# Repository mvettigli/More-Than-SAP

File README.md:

# More-Than-SAP

The projects starts from Ben Eater's SAP-1 build and improves memory availability and CPU functions.

Specifically it implements:
- 16-bit address bus addressable to data bus
- 16-bit stack pointer
- 16 bit program counter
- RAM 64 kByte using CY7C199
- ROM 32 kByte using AT28C256
- 8 bit instruction register
- 2 8-bit generic purpose registers
- 2 8-bit up/down counter registers with clear
- 2 8-bit shift registers with clear
- ALU with arithmetic (ADD, SUB) and logic functions (AND, OR, XOR)
- Register file of 4 units that can be addressed to ALU from 6 available
- 4-bit flag register: zero, sign, carry and overflow

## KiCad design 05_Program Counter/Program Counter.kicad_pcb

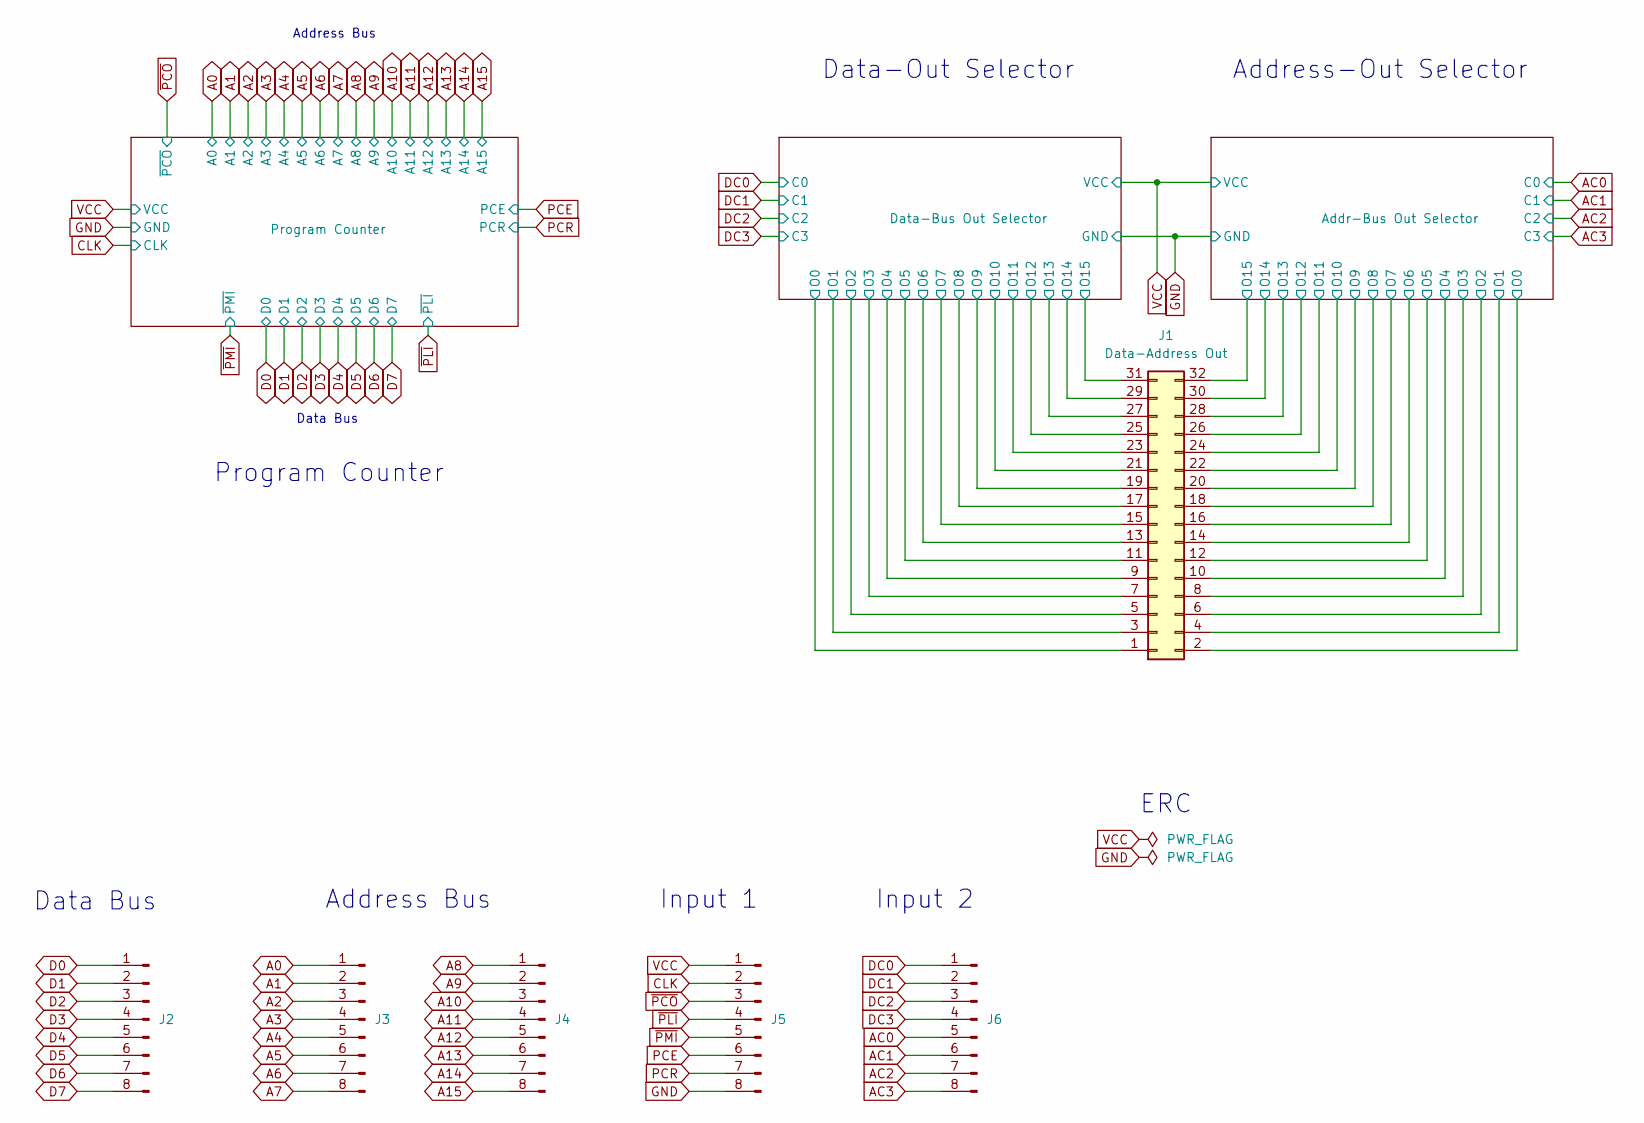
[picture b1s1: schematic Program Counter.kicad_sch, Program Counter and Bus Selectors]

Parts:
J1: Data-Address Out; PinHeader_2x16_P2.54mm_Horizontal
J2: Data bus; PinHeader_1x08_P2.54mm_Horizontal
J3: Address Bus 1; PinHeader_1x08_P2.54mm_Horizontal
J4: Address Bus 2; PinHeader_1x08_P2.54mm_Horizontal
J5: Input 1; PinHeader_1x08_P2.54mm_Horizontal
J6: Input 2; PinHeader_1x08_P2.54mm_Horizontal

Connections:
/Addr-Bus Out Selector/O0: J1.2; also elsewhere on the board
/Addr-Bus Out Selector/O1: J1.4; also elsewhere on the board
/Addr-Bus Out Selector/O2: J1.6; also elsewhere on the board
/Addr-Bus Out Selector/O3: J1.8; also elsewhere on the board
/Addr-Bus Out Selector/O4: J1.10; also elsewhere on the board
/Addr-Bus Out Selector/O5: J1.12; also elsewhere on the board
/Addr-Bus Out Selector/O6: J1.14; also elsewhere on the board
/Addr-Bus Out Selector/O7: J1.16; also elsewhere on the board
/Addr-Bus Out Selector/O8: J1.18; also elsewhere on the board
/Addr-Bus Out Selector/O9: J1.20; also elsewhere on the board
/Addr-Bus Out Selector/O10: J1.22; also elsewhere on the board
/Addr-Bus Out Selector/O11: J1.24; also elsewhere on the board
/Addr-Bus Out Selector/O12: J1.26; also elsewhere on the board
/Addr-Bus Out Selector/O13: J1.28; also elsewhere on the board
/Addr-Bus Out Selector/O14: J1.30; also elsewhere on the board
/Addr-Bus Out Selector/O15: J1.32; also elsewhere on the board
/Data-Bus Out Selector/O0: J1.1; also elsewhere on the board
/Data-Bus Out Selector/O1: J1.3; also elsewhere on the board
/Data-Bus Out Selector/O2: J1.5; also elsewhere on the board
/Data-Bus Out Selector/O3: J1.7; also elsewhere on the board
/Data-Bus Out Selector/O4: J1.9; also elsewhere on the board
/Data-Bus Out Selector/O5: J1.11; also elsewhere on the board
/Data-Bus Out Selector/O6: J1.13; also elsewhere on the board
/Data-Bus Out Selector/O7: J1.15; also elsewhere on the board
/Data-Bus Out Selector/O8: J1.17; also elsewhere on the board
/Data-Bus Out Selector/O9: J1.19; also elsewhere on the board
/Data-Bus Out Selector/O10: J1.21; also elsewhere on the board
/Data-Bus Out Selector/O11: J1.23; also elsewhere on the board
/Data-Bus Out Selector/O12: J1.25; also elsewhere on the board
/Data-Bus Out Selector/O13: J1.27; also elsewhere on the board
/Data-Bus Out Selector/O14: J1.29; also elsewhere on the board
/Data-Bus Out Selector/O15: J1.31; also elsewhere on the board
A0: J3.1; also elsewhere on the board
A1: J3.2; also elsewhere on the board
A2: J3.3; also elsewhere on the board
A3: J3.4; also elsewhere on the board
A4: J3.5; also elsewhere on the board
A5: J3.6; also elsewhere on the board
A6: J3.7; also elsewhere on the board
A7: J3.8; also elsewhere on the board
A8: J4.1; also elsewhere on the board
A9: J4.2; also elsewhere on the board
A10: J4.3; also elsewhere on the board
A11: J4.4; also elsewhere on the board
A12: J4.5; also elsewhere on the board
A13: J4.6; also elsewhere on the board
A14: J4.7; also elsewhere on the board
A15: J4.8; also elsewhere on the board
AC0: J6.5; also elsewhere on the board
AC1: J6.6; also elsewhere on the board
AC2: J6.7; also elsewhere on the board
AC3: J6.8; also elsewhere on the board
CLK: J5.2; also elsewhere on the board
D0: J2.1; also elsewhere on the board
D1: J2.2; also elsewhere on the board
D2: J2.3; also elsewhere on the board
D3: J2.4; also elsewhere on the board
D4: J2.5; also elsewhere on the board
D5: J2.6; also elsewhere on the board
D6: J2.7; also elsewhere on the board
D7: J2.8; also elsewhere on the board
DC0: J6.1; also elsewhere on the board
DC1: J6.2; also elsewhere on the board
DC2: J6.3; also elsewhere on the board
DC3: J6.4; also elsewhere on the board
GND: J5.8; also elsewhere on the board
PCE: J5.6; also elsewhere on the board
PCR: J5.7; also elsewhere on the board
VCC: J5.1; also elsewhere on the board
~PCO: J5.3; also elsewhere on the board
~PLI: J5.4; also elsewhere on the board
~PMI: J5.5; also elsewhere on the board

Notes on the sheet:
Address Bus
ERC
Address-Out Selector
Program Counter
Data Bus
Input 2
Data-Out Selector
Input 1

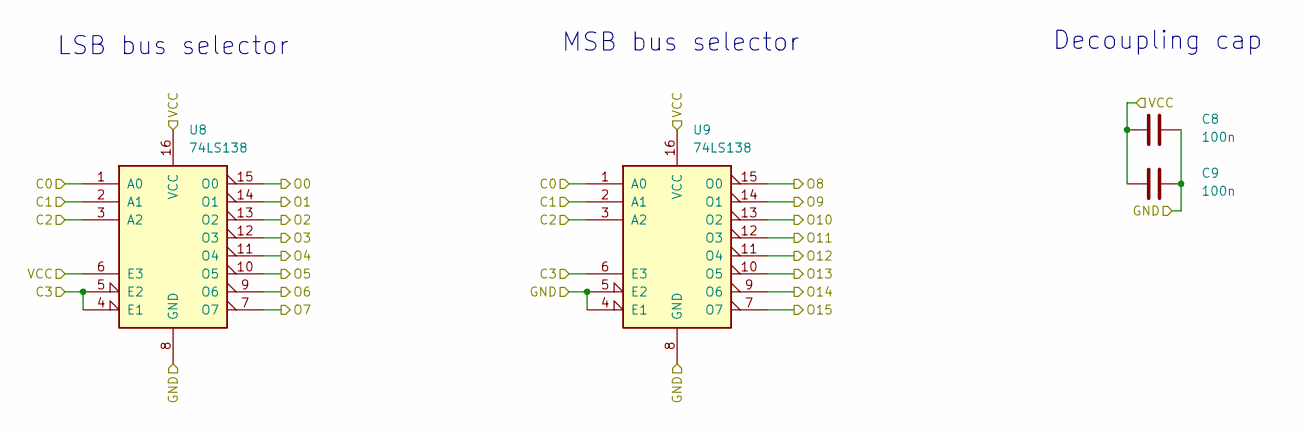
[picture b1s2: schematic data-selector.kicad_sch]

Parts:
C8, C9: 100n; C_Disc_D3.0mm_W1.6mm_P2.50mm
U8, U9: 74LS138; DIP-16_W7.62mm

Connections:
/Data-Bus Out Selector/O0: U8.15 (O0); also elsewhere on the board
/Data-Bus Out Selector/O1: U8.14 (O1); also elsewhere on the board
/Data-Bus Out Selector/O2: U8.13 (O2); also elsewhere on the board
/Data-Bus Out Selector/O3: U8.12 (O3); also elsewhere on the board
/Data-Bus Out Selector/O4: U8.11 (O4); also elsewhere on the board
/Data-Bus Out Selector/O5: U8.10 (O5); also elsewhere on the board
/Data-Bus Out Selector/O6: U8.9 (O6); also elsewhere on the board
/Data-Bus Out Selector/O7: U8.7 (O7); also elsewhere on the board
/Data-Bus Out Selector/O8: U9.15 (O0); also elsewhere on the board
/Data-Bus Out Selector/O9: U9.14 (O1); also elsewhere on the board
/Data-Bus Out Selector/O10: U9.13 (O2); also elsewhere on the board
/Data-Bus Out Selector/O11: U9.12 (O3); also elsewhere on the board
/Data-Bus Out Selector/O12: U9.11 (O4); also elsewhere on the board
/Data-Bus Out Selector/O13: U9.10 (O5); also elsewhere on the board
/Data-Bus Out Selector/O14: U9.9 (O6); also elsewhere on the board
/Data-Bus Out Selector/O15: U9.7 (O7); also elsewhere on the board
DC0: U8.1 (A0), U9.1 (A0); also elsewhere on the board
DC1: U8.2 (A1), U9.2 (A1); also elsewhere on the board
DC2: U8.3 (A2), U9.3 (A2); also elsewhere on the board
DC3: U8.4 (E1), U8.5 (E2), U9.6 (E3); also elsewhere on the board
GND: C8.2, C9.2, U8.8 (GND), U9.4 (E1), U9.5 (E2), U9.8 (GND); also elsewhere on the board
VCC: C8.1, C9.1, U8.6 (E3), U8.16 (VCC), U9.16 (VCC); also elsewhere on the board

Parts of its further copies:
C10, C11: 100n; C_Disc_D3.0mm_W1.6mm_P2.50mm
U10, U11: 74LS138; DIP-16_W7.62mm

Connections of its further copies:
/Addr-Bus Out Selector/O0: U10.15 (O0); also elsewhere on the board
/Addr-Bus Out Selector/O1: U10.14 (O1); also elsewhere on the board
/Addr-Bus Out Selector/O2: U10.13 (O2); also elsewhere on the board
/Addr-Bus Out Selector/O3: U10.12 (O3); also elsewhere on the board
/Addr-Bus Out Selector/O4: U10.11 (O4); also elsewhere on the board
/Addr-Bus Out Selector/O5: U10.10 (O5); also elsewhere on the board
/Addr-Bus Out Selector/O6: U10.9 (O6); also elsewhere on the board
/Addr-Bus Out Selector/O7: U10.7 (O7); also elsewhere on the board
/Addr-Bus Out Selector/O8: U11.15 (O0); also elsewhere on the board
/Addr-Bus Out Selector/O9: U11.14 (O1); also elsewhere on the board
/Addr-Bus Out Selector/O10: U11.13 (O2); also elsewhere on the board
/Addr-Bus Out Selector/O11: U11.12 (O3); also elsewhere on the board
/Addr-Bus Out Selector/O12: U11.11 (O4); also elsewhere on the board
/Addr-Bus Out Selector/O13: U11.10 (O5); also elsewhere on the board
/Addr-Bus Out Selector/O14: U11.9 (O6); also elsewhere on the board
/Addr-Bus Out Selector/O15: U11.7 (O7); also elsewhere on the board
AC0: U10.1 (A0), U11.1 (A0); also elsewhere on the board
AC1: U10.2 (A1), U11.2 (A1); also elsewhere on the board
AC2: U10.3 (A2), U11.3 (A2); also elsewhere on the board
AC3: U10.4 (E1), U10.5 (E2), U11.6 (E3); also elsewhere on the board
GND: C10.2, C11.2, U10.8 (GND), U11.4 (E1), U11.5 (E2), U11.8 (GND); also elsewhere on the board
VCC: C10.1, C11.1, U10.6 (E3), U10.16 (VCC), U11.16 (VCC); also elsewhere on the board

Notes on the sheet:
Decoupling cap
LSB bus selector
MSB bus selector

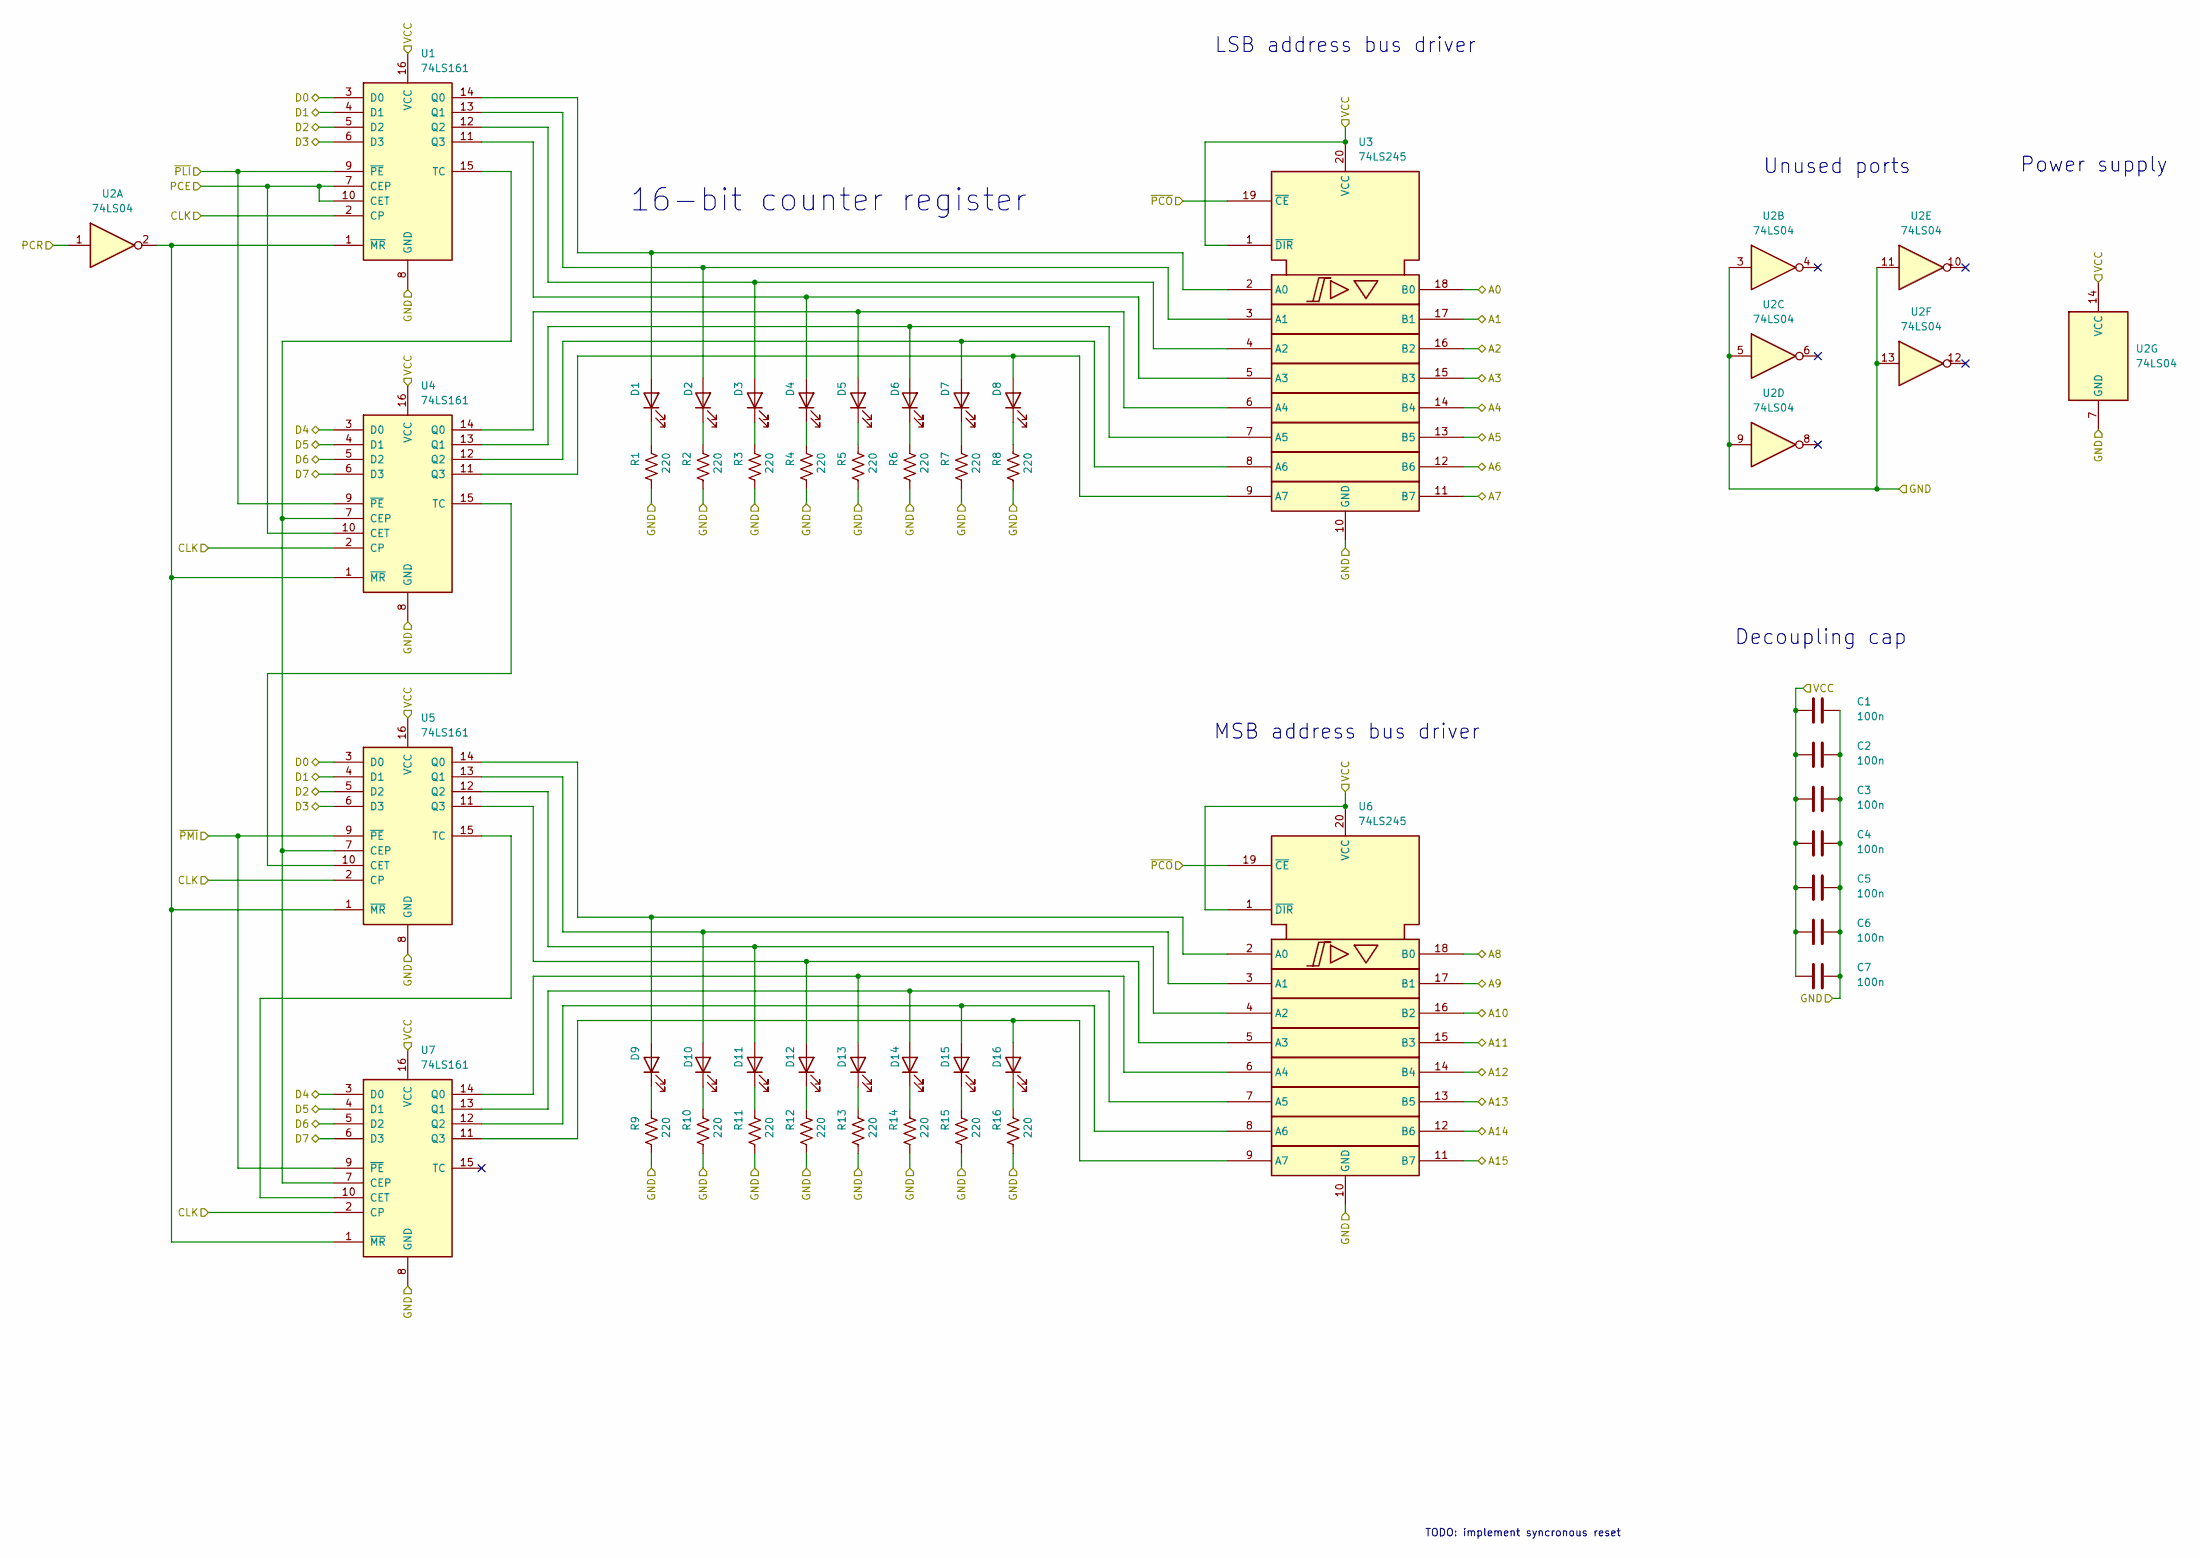
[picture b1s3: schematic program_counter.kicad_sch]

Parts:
C1, C2, C3, C4, C5, C6, C7: 100n; C_Disc_D3.0mm_W1.6mm_P2.50mm
D1, D2, D3, D4, D5, D6, D7, D8, D9, D10, D11, D12, D13, D14, D15, D16: GREEN; LED_D3.0mm
R1, R2, R3, R4, R5, R6, R7, R8, R9, R10, R11, R12, R13, R14, R15, R16: 220; R_Axial_DIN0207_L6.3mm_D2.5mm_P10.16mm_Horizontal
U1, U4, U5, U7: 74LS161; DIP-16_W7.62mm
U2: 74LS04; DIP-14_W7.62mm
U3, U6: 74LS245; DIP-20_W7.62mm

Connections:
A0: U3.18 (B0); also elsewhere on the board
A1: U3.17 (B1); also elsewhere on the board
A2: U3.16 (B2); also elsewhere on the board
A3: U3.15 (B3); also elsewhere on the board
A4: U3.14 (B4); also elsewhere on the board
A5: U3.13 (B5); also elsewhere on the board
A6: U3.12 (B6); also elsewhere on the board
A7: U3.11 (B7); also elsewhere on the board
A8: U6.18 (B0); also elsewhere on the board
A9: U6.17 (B1); also elsewhere on the board
A10: U6.16 (B2); also elsewhere on the board
A11: U6.15 (B3); also elsewhere on the board
A12: U6.14 (B4); also elsewhere on the board
A13: U6.13 (B5); also elsewhere on the board
A14: U6.12 (B6); also elsewhere on the board
A15: U6.11 (B7); also elsewhere on the board
CLK: U1.2 (CP), U4.2 (CP), U5.2 (CP), U7.2 (CP); also elsewhere on the board
D0: U1.3 (D0), U5.3 (D0); also elsewhere on the board
D1: U1.4 (D1), U5.4 (D1); also elsewhere on the board
D2: U1.5 (D2), U5.5 (D2); also elsewhere on the board
D3: U1.6 (D3), U5.6 (D3); also elsewhere on the board
D4: U4.3 (D0), U7.3 (D0); also elsewhere on the board
D5: U4.4 (D1), U7.4 (D1); also elsewhere on the board
D6: U4.5 (D2), U7.5 (D2); also elsewhere on the board
D7: U4.6 (D3), U7.6 (D3); also elsewhere on the board
GND: C1.2, C2.2, C3.2, C4.2, C5.2, C6.2, C7.2, R1.2, R2.2, R3.2, R4.2, R5.2, R6.2, R7.2, R8.2, R9.2, R10.2, R11.2, R12.2, R13.2, R14.2, R15.2, R16.2, U1.8 (GND), U2.3, U2.5, U2.7 (GND), U2.9, U2.11, U2.13, U3.10 (GND), U4.8 (GND), U5.8 (GND), U6.10 (GND), U7.8 (GND); also elsewhere on the board
unnamed: D1.2 (A), U1.14 (Q0), U3.2 (A0)
unnamed: D1.1 (K), R1.1
unnamed: D2.2 (A), U1.13 (Q1), U3.3 (A1)
unnamed: D2.1 (K), R2.1
unnamed: D3.2 (A), U1.12 (Q2), U3.4 (A2)
unnamed: D3.1 (K), R3.1
unnamed: D4.2 (A), U1.11 (Q3), U3.5 (A3)
unnamed: D4.1 (K), R4.1
unnamed: D5.2 (A), U3.6 (A4), U4.14 (Q0)
unnamed: D5.1 (K), R5.1
unnamed: D6.2 (A), U3.7 (A5), U4.13 (Q1)
unnamed: D6.1 (K), R6.1
unnamed: D7.2 (A), U3.8 (A6), U4.12 (Q2)
unnamed: D7.1 (K), R7.1
unnamed: D8.2 (A), U3.9 (A7), U4.11 (Q3)
unnamed: D8.1 (K), R8.1
unnamed: D9.2 (A), U5.14 (Q0), U6.2 (A0)
unnamed: D9.1 (K), R9.1
unnamed: D10.2 (A), U5.13 (Q1), U6.3 (A1)
unnamed: D10.1 (K), R10.1
unnamed: D11.2 (A), U5.12 (Q2), U6.4 (A2)
unnamed: D11.1 (K), R11.1
unnamed: D12.2 (A), U5.11 (Q3), U6.5 (A3)
unnamed: D12.1 (K), R12.1
unnamed: D13.2 (A), U6.6 (A4), U7.14 (Q0)
unnamed: D13.1 (K), R13.1
unnamed: D14.2 (A), U6.7 (A5), U7.13 (Q1)
unnamed: D14.1 (K), R14.1
unnamed: D15.2 (A), U6.8 (A6), U7.12 (Q2)
unnamed: D15.1 (K), R15.1
unnamed: D16.2 (A), U6.9 (A7), U7.11 (Q3)
unnamed: D16.1 (K), R16.1
unnamed: U1.15 (TC), U4.7 (CEP), U5.7 (CEP), U7.7 (CEP)
unnamed: U1.1 (~MR), U2.2, U4.1 (~MR), U5.1 (~MR), U7.1 (~MR)
unnamed: U4.15 (TC), U5.10 (CET)
unnamed: U5.15 (TC), U7.10 (CET)
PCE: U1.7 (CEP), U1.10 (CET), U4.10 (CET); also elsewhere on the board
PCR: U2.1; also elsewhere on the board
VCC: C1.1, C2.1, C3.1, C4.1, C5.1, C6.1, C7.1, U1.16 (VCC), U2.14 (VCC), U3.1 (~DIR), U3.20 (VCC), U4.16 (VCC), U5.16 (VCC), U6.1 (~DIR), U6.20 (VCC), U7.16 (VCC); also elsewhere on the board
~PCO: U3.19 (~CE), U6.19 (~CE); also elsewhere on the board
~PLI: U1.9 (~PE), U4.9 (~PE); also elsewhere on the board
~PMI: U5.9 (~PE), U7.9 (~PE); also elsewhere on the board

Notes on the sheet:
Unused ports
Power supply
Decoupling cap
16-bit counter register
MSB address bus driver
LSB address bus driver
TODO: implement syncronous reset

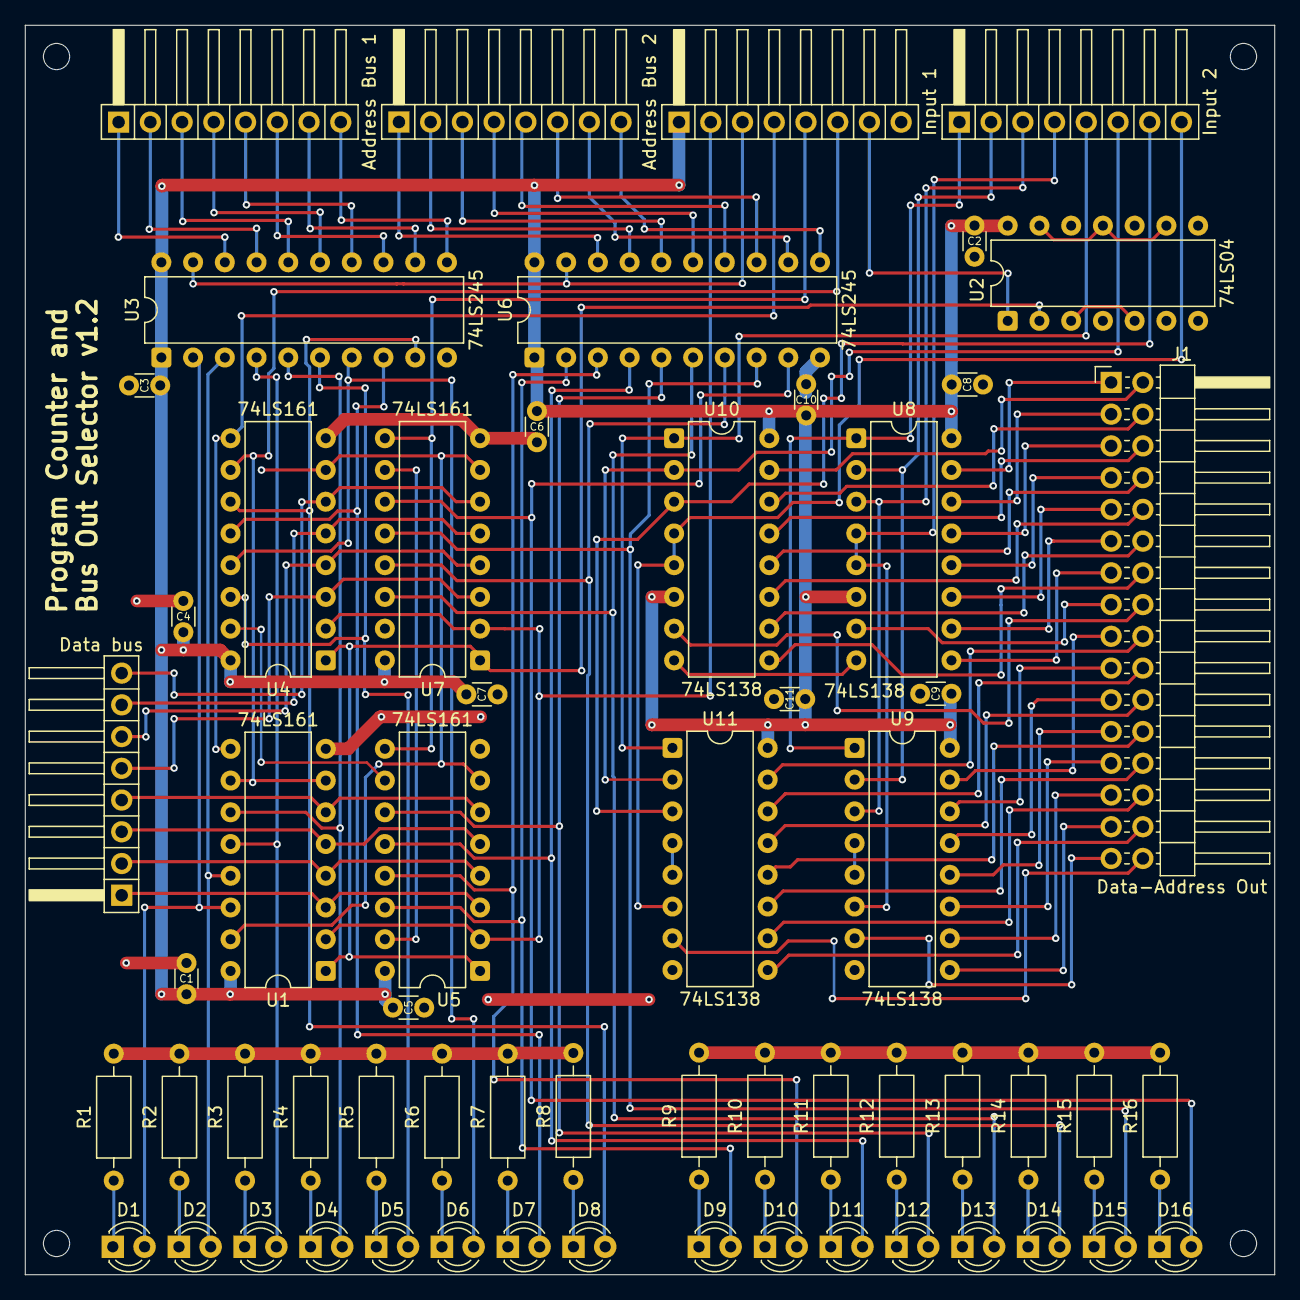
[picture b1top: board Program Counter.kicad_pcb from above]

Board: 2 copper layers, 100.0 x 100.0 mm, 60 parts (0 on the bottom side), 108 nets.

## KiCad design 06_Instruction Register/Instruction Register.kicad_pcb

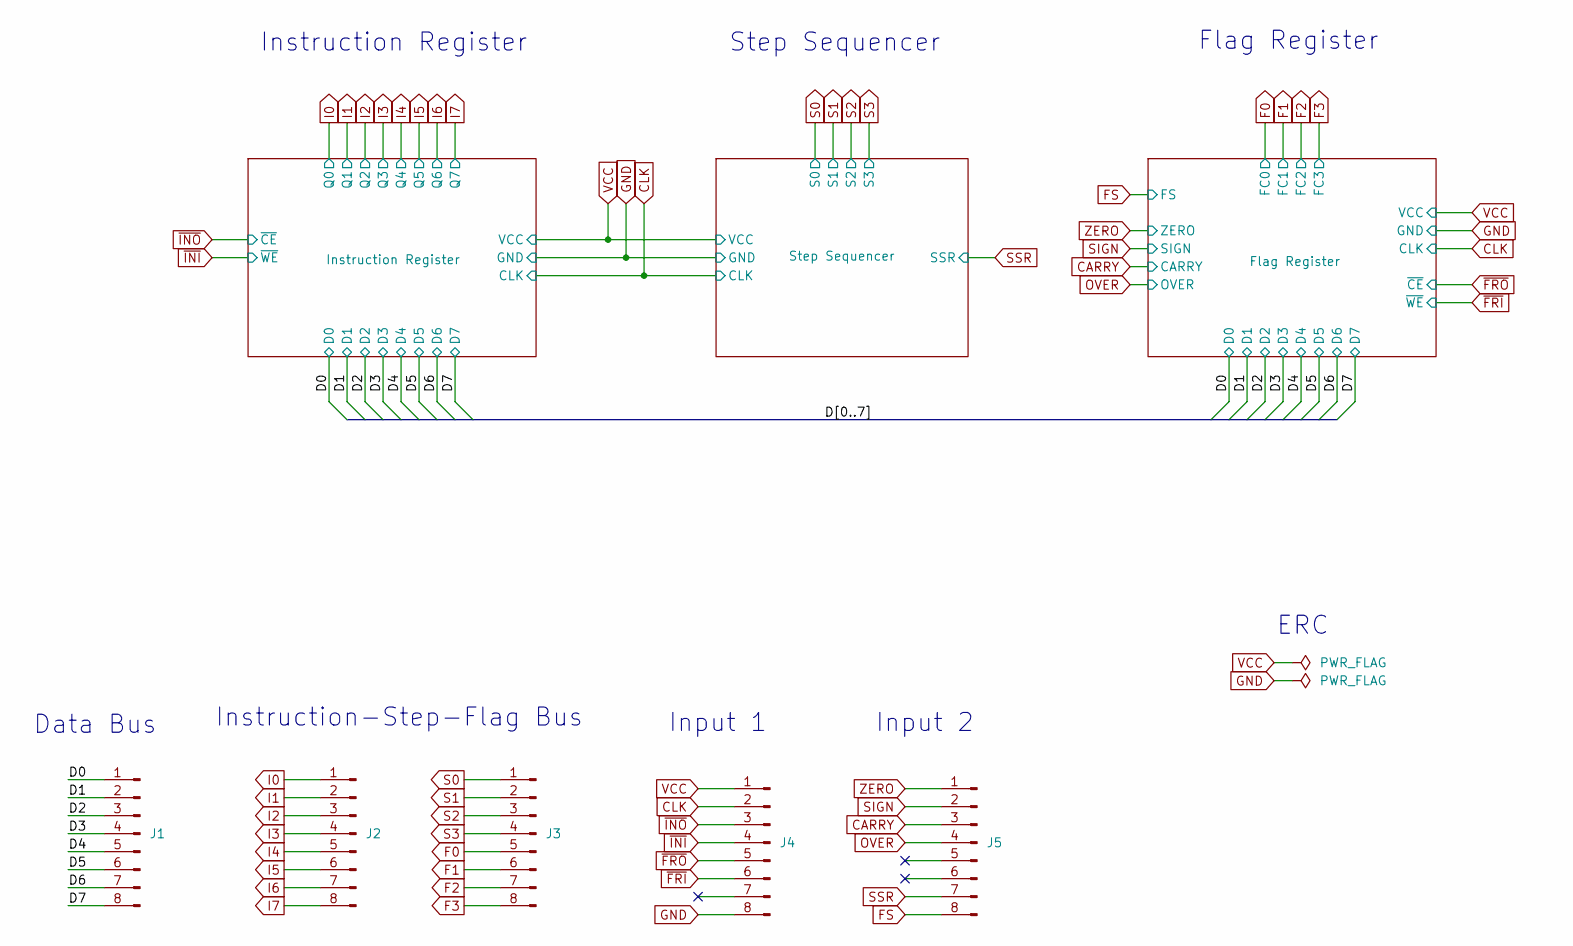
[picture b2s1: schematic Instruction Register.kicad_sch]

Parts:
J1: Data bus; PinHeader_1x08_P2.54mm_Horizontal
J2: Instruction Bus; PinHeader_1x08_P2.54mm_Horizontal
J3: Step-Flag Bus; PinHeader_1x08_P2.54mm_Horizontal
J4: Input 1; PinHeader_1x08_P2.54mm_Horizontal
J5: Input 2; PinHeader_1x08_P2.54mm_Horizontal

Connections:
/D0: J1.1; also elsewhere on the board
/D1: J1.2; also elsewhere on the board
/D2: J1.3; also elsewhere on the board
/D3: J1.4; also elsewhere on the board
/D4: J1.5; also elsewhere on the board
/D5: J1.6; also elsewhere on the board
/D6: J1.7; also elsewhere on the board
/D7: J1.8; also elsewhere on the board
CARRY: J5.3; also elsewhere on the board
CLK: J4.2; also elsewhere on the board
F0: J3.5; also elsewhere on the board
F1: J3.6; also elsewhere on the board
F2: J3.7; also elsewhere on the board
F3: J3.8; also elsewhere on the board
FS: J5.8; also elsewhere on the board
GND: J4.8; also elsewhere on the board
I0: J2.1; also elsewhere on the board
I1: J2.2; also elsewhere on the board
I2: J2.3; also elsewhere on the board
I3: J2.4; also elsewhere on the board
I4: J2.5; also elsewhere on the board
I5: J2.6; also elsewhere on the board
I6: J2.7; also elsewhere on the board
I7: J2.8; also elsewhere on the board
OVER: J5.4; also elsewhere on the board
S0: J3.1; also elsewhere on the board
S1: J3.2; also elsewhere on the board
S2: J3.3; also elsewhere on the board
S3: J3.4; also elsewhere on the board
SIGN: J5.2; also elsewhere on the board
SSR: J5.7; also elsewhere on the board
VCC: J4.1; also elsewhere on the board
ZERO: J5.1; also elsewhere on the board
~FRI: J4.6; also elsewhere on the board
~FRO: J4.5; also elsewhere on the board
~INI: J4.4; also elsewhere on the board
~INO: J4.3; also elsewhere on the board

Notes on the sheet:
Instruction-Step-Flag Bus
Instruction Register
Data Bus
Step Sequencer
ERC
Flag Register
Input 2
Input 1

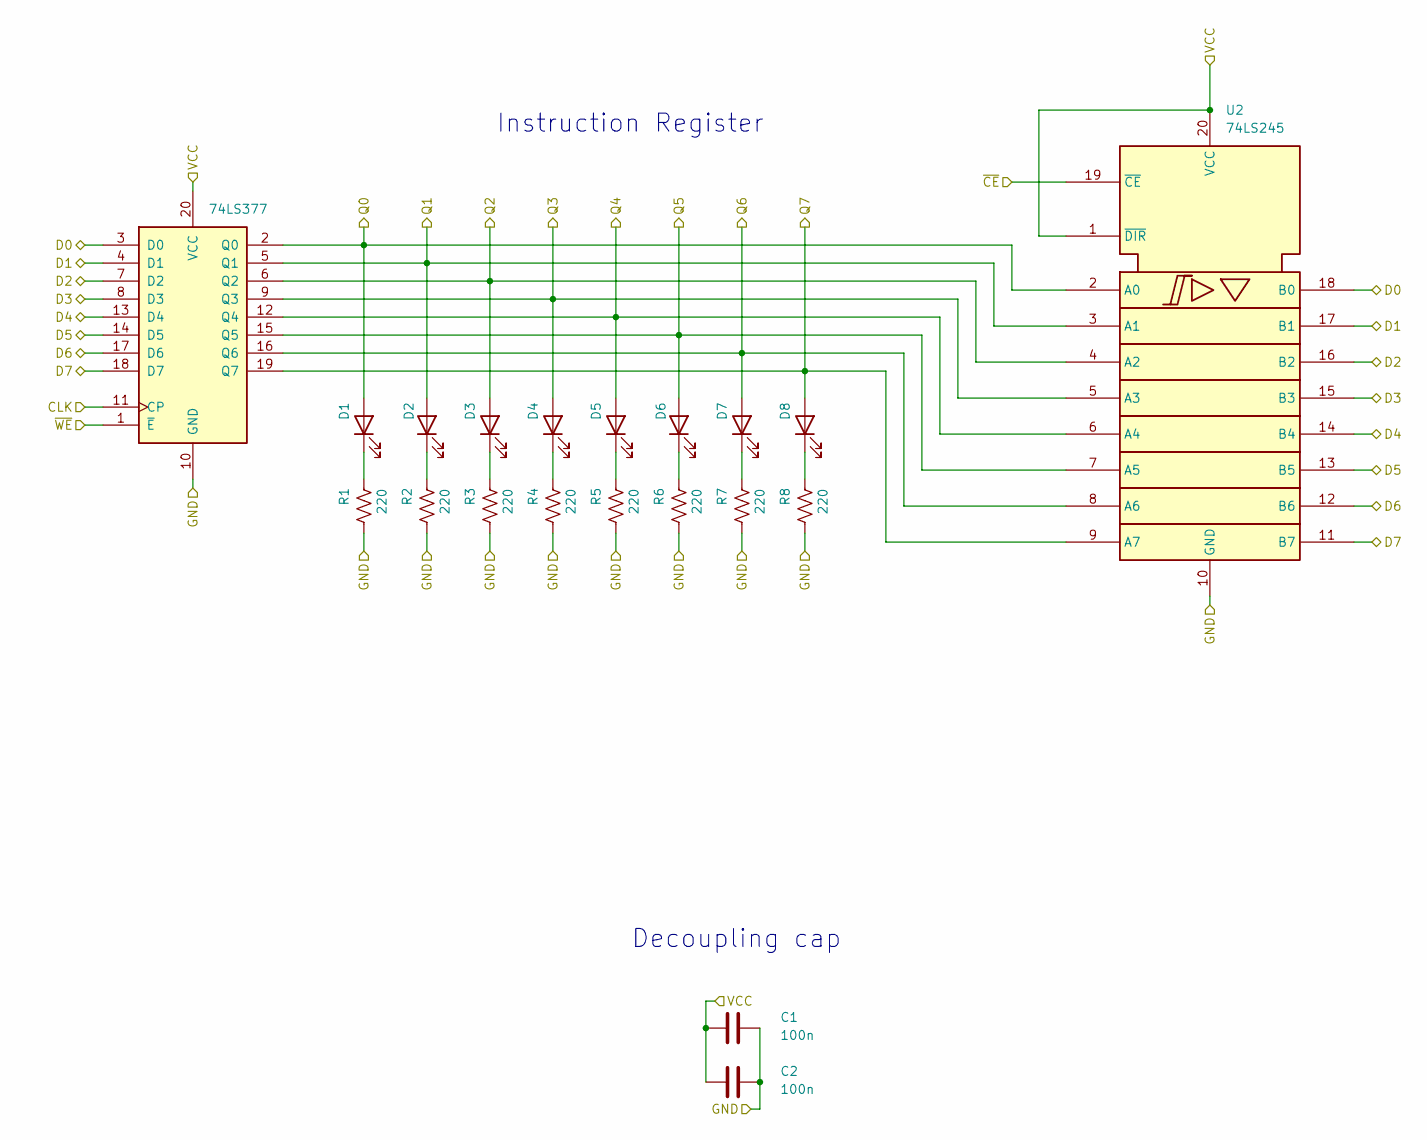
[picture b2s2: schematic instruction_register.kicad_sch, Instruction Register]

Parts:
C1, C2: 100n; C_Disc_D3.0mm_W1.6mm_P2.50mm
D1, D2, D3, D4, D5, D6, D7, D8: RED; LED_D3.0mm
R1, R2, R3, R4, R5, R6, R7, R8: 220; R_Axial_DIN0207_L6.3mm_D2.5mm_P10.16mm_Horizontal
U1: 74LS377; DIP-20_W7.62mm
U2: 74LS245; DIP-20_W7.62mm

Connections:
/D0: U1.3 (D0), U2.18 (B0); also elsewhere on the board
/D1: U1.4 (D1), U2.17 (B1); also elsewhere on the board
/D2: U1.7 (D2), U2.16 (B2); also elsewhere on the board
/D3: U1.8 (D3), U2.15 (B3); also elsewhere on the board
/D4: U1.13 (D4), U2.14 (B4); also elsewhere on the board
/D5: U1.14 (D5), U2.13 (B5); also elsewhere on the board
/D6: U1.17 (D6), U2.12 (B6); also elsewhere on the board
/D7: U1.18 (D7), U2.11 (B7); also elsewhere on the board
CLK: U1.11 (CP); also elsewhere on the board
GND: C1.2, C2.2, R1.2, R2.2, R3.2, R4.2, R5.2, R6.2, R7.2, R8.2, U1.10 (GND), U2.10 (GND); also elsewhere on the board
I0: D1.2 (A), U1.2 (Q0), U2.2 (A0); also elsewhere on the board
I1: D2.2 (A), U1.5 (Q1), U2.3 (A1); also elsewhere on the board
I2: D3.2 (A), U1.6 (Q2), U2.4 (A2); also elsewhere on the board
I3: D4.2 (A), U1.9 (Q3), U2.5 (A3); also elsewhere on the board
I4: D5.2 (A), U1.12 (Q4), U2.6 (A4); also elsewhere on the board
I5: D6.2 (A), U1.15 (Q5), U2.7 (A5); also elsewhere on the board
I6: D7.2 (A), U1.16 (Q6), U2.8 (A6); also elsewhere on the board
I7: D8.2 (A), U1.19 (Q7), U2.9 (A7); also elsewhere on the board
unnamed: D1.1 (K), R1.1
unnamed: D2.1 (K), R2.1
unnamed: D3.1 (K), R3.1
unnamed: D4.1 (K), R4.1
unnamed: D5.1 (K), R5.1
unnamed: D6.1 (K), R6.1
unnamed: D7.1 (K), R7.1
unnamed: D8.1 (K), R8.1
VCC: C1.1, C2.1, U1.20 (VCC), U2.1 (~DIR), U2.20 (VCC); also elsewhere on the board
~INI: U1.1 (~E); also elsewhere on the board
~INO: U2.19 (~CE); also elsewhere on the board

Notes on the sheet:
Decoupling cap
Instruction Register

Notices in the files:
09_Stack Pointer/Stack Pointer.kicad_sch:
By using or distributing it, you accept the terms of the GPL.
It comes with absolutely NO WARRANTY; for details, see the full license.
This software is licensed under the GNU General Public License (GPL).
